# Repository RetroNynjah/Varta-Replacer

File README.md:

# Varta Replacer

<br/>

This simple circuit enables use of a coin-cell battery in place of a dangerous leaky Varta battery in your favorite vintage computer. 
This kind of device has many names but is often called Varta Replace. Varta Killer or similar because Varta rechargable batteries were common in many old computers including many of the Commodore Amiga computers. Those old Varta batteries are famous for leaking with severe corrosion as a result.

<br/>

## Mounting footprint
This is the footprint of the mounting pins. Make sure that they match your installation well enough.  
The mounting pins can be bent a bit to fit other footprints if they are close enough.

<br/>
Measurements are in millimeters.

## Soldering
Start by soldering all components on the bottom side. Add whatever mounting pins you need for your installation. If you don't know what you will use the bord for you should install all four pins and trim off the ones you don't need when installing the board.
You normally want to use the current limiting resistor R1 so always include the resistor in your build. If you must skip the resistor later for some reason you can bypass the resistor using solder jumper SJ1.

## BOM
|Pcs|Identifier |Part                 |Value       |Comments                         |
|---|----------	|----------	          |-----       |-----							               |
|1  |R1         |Resistor             |220 Ohm     |                                 |
|1  |D1         |Rectifier diode      |1N4148      |                                 |
|1  |BT1        |Battery holder       |CR2032      |20 mm pitch                      |
|4  |           |Mounting pins        |            |Regular pin headers 4 single pins|

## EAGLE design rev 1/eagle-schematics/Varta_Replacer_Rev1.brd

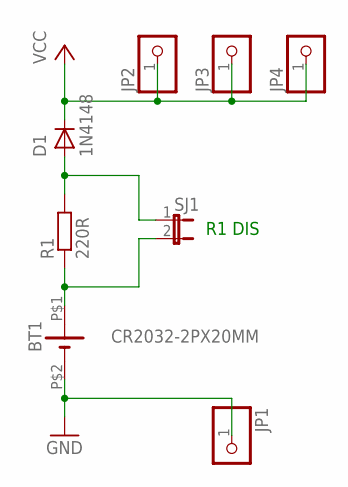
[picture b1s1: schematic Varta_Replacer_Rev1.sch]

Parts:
BT1: CR2032-2PX20MM; CR2032_2PX20
D1: 1N4148; DO-1N4148
JP1, JP2, JP3, JP4: PINHD-1X1; 1X01
R1: 220R; 0207/10
SJ1: JUMPER-2SJ; SJ-2

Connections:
BAT+: BT1.P$1 (+), R1.1, SJ1.2
GND: BT1.P$2 (-), JP1.1
unnamed: D1.A, R1.2, SJ1.1
VCC: D1.C, JP2.1, JP3.1, JP4.1

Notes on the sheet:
R1 DIS

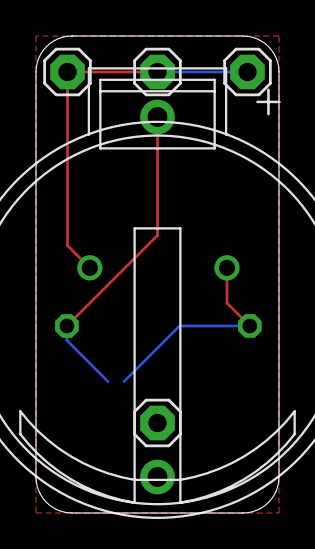
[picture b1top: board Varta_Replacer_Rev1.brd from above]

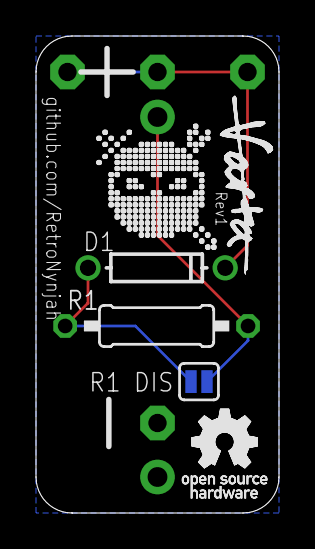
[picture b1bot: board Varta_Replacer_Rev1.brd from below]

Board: 2 copper layers, 13.5 x 26.5 mm, 11 parts (6 on the bottom side), 4 nets.

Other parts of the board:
!VARTA: !VARTA_10X3
U$1: RETRONINJA_NOTEXT_7MM
U$2: OSHW_5MM

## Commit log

2022-04-03 Initial upload
